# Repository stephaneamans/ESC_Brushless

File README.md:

# ESC brushless

## General principle

The electronic speed controler (ESC) is used to control the rotation and speed of a brushless motor.

Brushless motors are widely used in lot of applications.

The system is based around a microcontroler controlling a gate driver in charge of switching on and of MOS FET to power the motors inductors (see the principle the the hardware section).
The rotor position and general other informations are sent back to the microcontroller to help it to detect the appropriate timming of commutation.
The microcontroller takes informations through a bus link from the master system, mainly to know the motor speed to apply.
It can send back some informations like, current consumption, acknowledges, diagnostics and so on.

[Hardware architecture documentation](./01-documentation/hardware_architecture.md)

[Software architecture documentation](./01-documentation/software_architecture.md)

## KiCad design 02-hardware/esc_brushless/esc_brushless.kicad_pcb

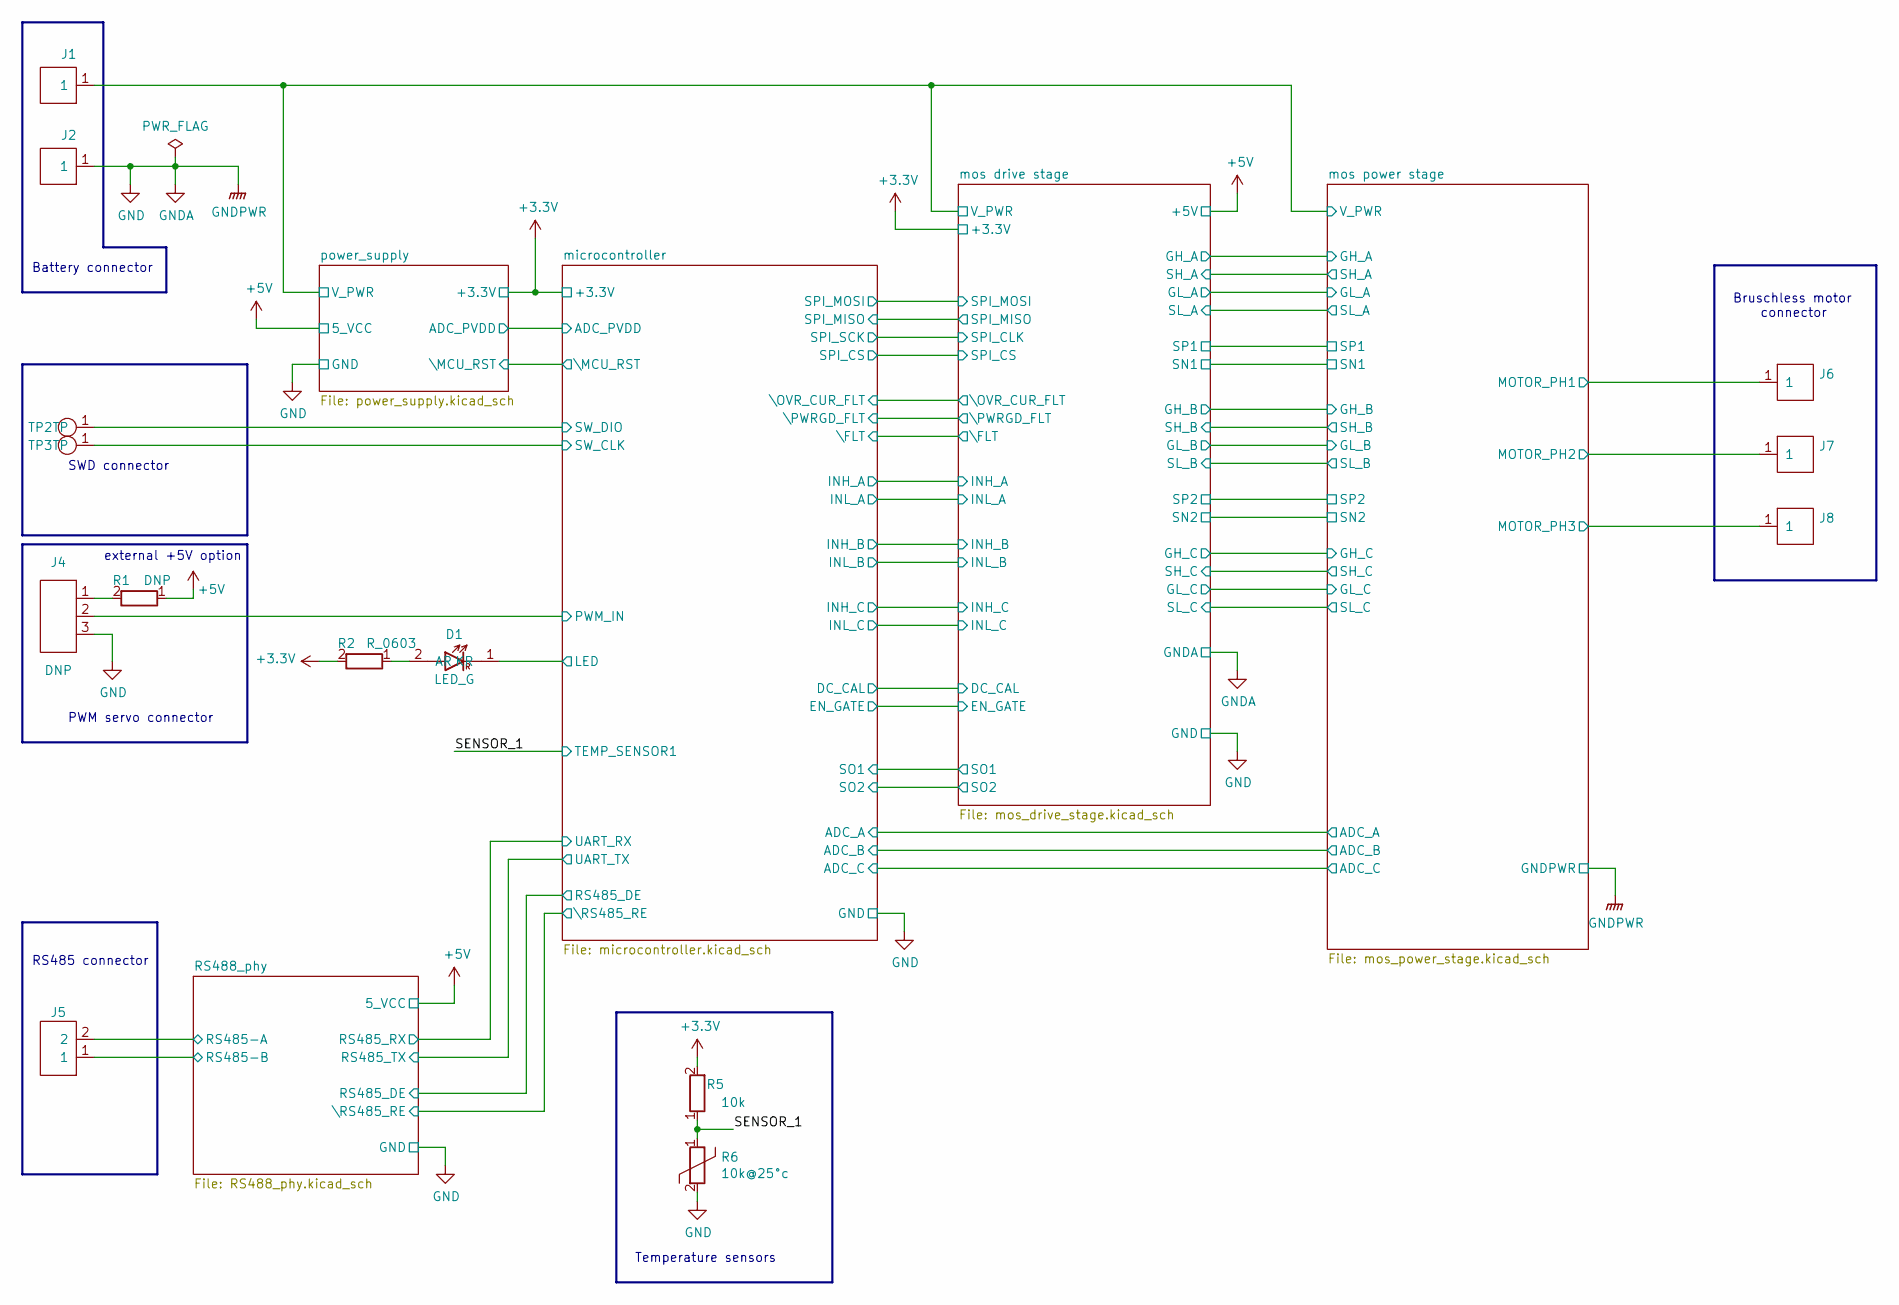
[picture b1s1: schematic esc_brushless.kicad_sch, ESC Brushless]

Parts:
D1: LED_G; LED_0603_1608Metric
J1, J2: Conn_HE13_1x1_5.08V; PinHeader_1x01_P5.08mm_Vertical
J4: DNP; PinHeader_1x03_P2.54mm_Vertical
J5: Conn_HE13_1x2_2.54V; PinHeader_1x02_P2.54mm_Vertical
J6, J7, J8: DNP; PinHeader_1x01_P5.08mm_Vertical
R1: DNP; R_0603_1608Metric_Pad0.98x0.95mm_HandSolder
R2: R_0603; R_0603_1608Metric_Pad0.98x0.95mm_HandSolder
R5: 10k; R_0603_1608Metric_Pad0.98x0.95mm_HandSolder
R6: 10k@25°c; R_0603_1608Metric_Pad0.98x0.95mm_HandSolder
TP2, TP3: test_point_smd; TP_SMD_1.25mm

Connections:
+3.3V: R2.2, R5.2; also elsewhere on the board
+5V: R1.1; also elsewhere on the board
/RS488_phy/RS485-A: J5.2; also elsewhere on the board
/RS488_phy/RS485-B: J5.1; also elsewhere on the board
/SENSOR_1: R5.1, R6.1; also elsewhere on the board
/microcontroller/LED: D1.1 (KR); also elsewhere on the board
/microcontroller/PWM_IN: J4.2; also elsewhere on the board
/microcontroller/SW_CLK: TP3.1 (TP); also elsewhere on the board
/microcontroller/SW_DIO: TP2.1 (TP); also elsewhere on the board
/mos drive stage/SH_A: J6.1; also elsewhere on the board
/mos drive stage/SH_B: J7.1; also elsewhere on the board
/mos drive stage/SH_C: J8.1; also elsewhere on the board
/mos drive stage/V_PWR: J1.1; also elsewhere on the board
GND: J2.1, J4.3, R6.2; also elsewhere on the board
unnamed: D1.2 (AR), R2.1
unnamed: J4.1, R1.2

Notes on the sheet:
Bruschless motor connector
SWD connector
PWM servo connector
RS485 connector
Temperature sensors
external +5V option
Battery connector

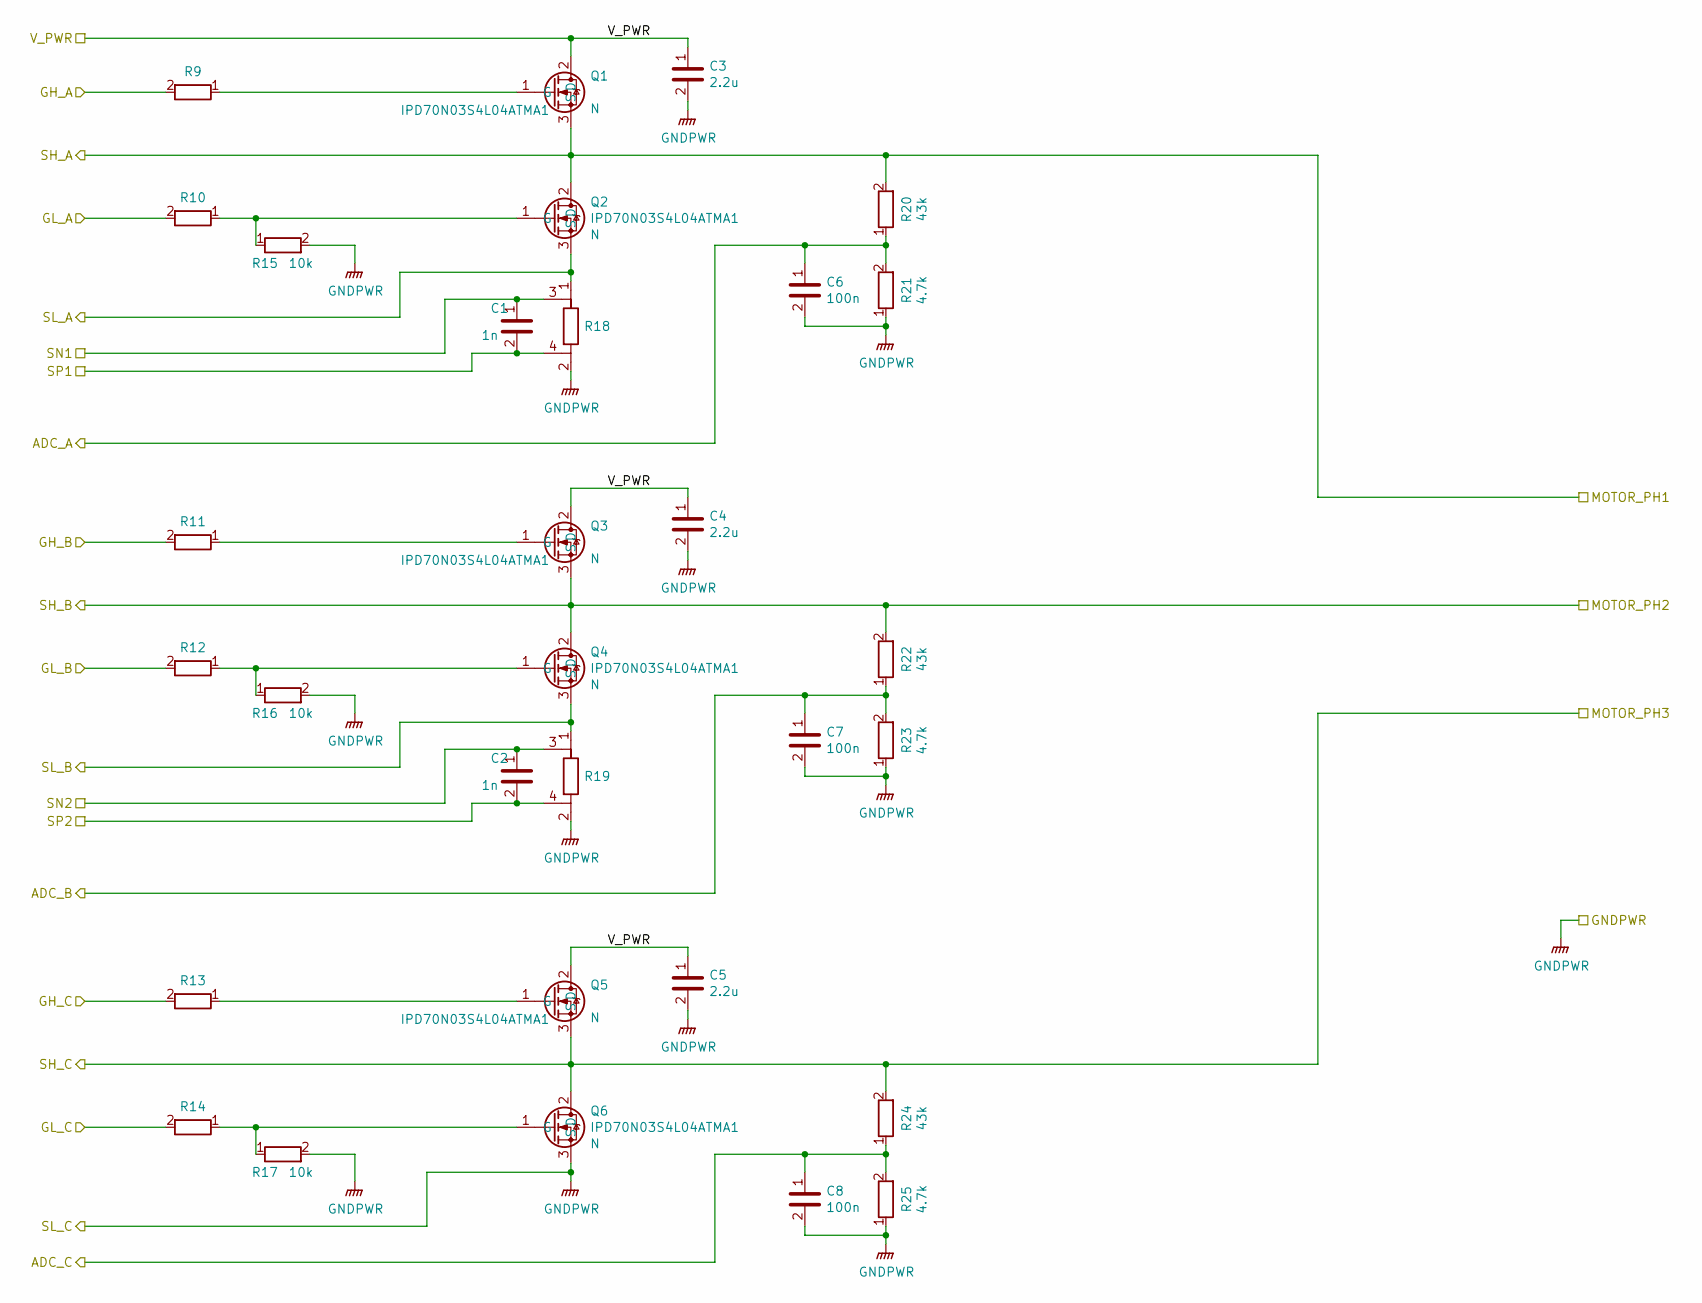
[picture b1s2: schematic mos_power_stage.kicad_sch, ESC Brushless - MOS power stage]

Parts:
C1, C2: 1n; C_0603_1608Metric_Pad1.08x0.95mm_HandSolder
C3, C4, C5: 2.2u; C_1210_3225Metric_Pad1.33x2.70mm_HandSolder
C6, C7, C8: 100n; C_0805_2012Metric_Pad1.18x1.45mm_HandSolder
Q1, Q2, Q3, Q4, Q5, Q6: IPD70N03S4L04ATMA1; TO-252-pin_1_3_TabPin2
R9, R10, R11, R12, R13, R14: R_0603; R_0603_1608Metric_Pad0.98x0.95mm_HandSolder
R15, R16, R17: 10k; R_0603_1608Metric_Pad0.98x0.95mm_HandSolder
R18, R19: R_shunt_2512; R_2512_6332Metric_shunt
R20, R22, R24: 43k; R_0603_1608Metric_Pad0.98x0.95mm_HandSolder
R21, R23, R25: 4.7k; R_0603_1608Metric_Pad0.98x0.95mm_HandSolder

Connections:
/microcontroller/ADC_A: C6.1, R20.1, R21.2; also elsewhere on the board
/microcontroller/ADC_B: C7.1, R22.1, R23.2; also elsewhere on the board
/microcontroller/ADC_C: C8.1, R24.1, R25.2; also elsewhere on the board
/mos drive stage/GH_A: R9.2; also elsewhere on the board
/mos drive stage/GH_B: R11.2; also elsewhere on the board
/mos drive stage/GH_C: R13.2; also elsewhere on the board
/mos drive stage/GL_A: R10.2; also elsewhere on the board
/mos drive stage/GL_B: R12.2; also elsewhere on the board
/mos drive stage/GL_C: R14.2; also elsewhere on the board
/mos drive stage/SH_A: Q1.3 (S), Q2.2 (D), R20.2; also elsewhere on the board
/mos drive stage/SH_B: Q3.3 (S), Q4.2 (D), R22.2; also elsewhere on the board
/mos drive stage/SH_C: Q5.3 (S), Q6.2 (D), R24.2; also elsewhere on the board
/mos drive stage/SL_A: Q2.3 (S), R18.1; also elsewhere on the board
/mos drive stage/SL_B: Q4.3 (S), R19.1; also elsewhere on the board
/mos drive stage/SN1: C1.1, R18.3; also elsewhere on the board
/mos drive stage/SN2: C2.1, R19.3; also elsewhere on the board
/mos drive stage/SP1: C1.2, R18.4; also elsewhere on the board
/mos drive stage/SP2: C2.2, R19.4; also elsewhere on the board
/mos drive stage/V_PWR: C3.1, C4.1, C5.1, Q1.2 (D), Q3.2 (D), Q5.2 (D); also elsewhere on the board
GND: C3.2, C4.2, C5.2, C6.2, C7.2, C8.2, Q6.3 (S), R15.2, R16.2, R17.2, R18.2, R19.2, R21.1, R23.1, R25.1; also elsewhere on the board
unnamed: Q1.1 (G), R9.1
unnamed: Q2.1 (G), R10.1, R15.1
unnamed: Q3.1 (G), R11.1
unnamed: Q4.1 (G), R12.1, R16.1
unnamed: Q5.1 (G), R13.1
unnamed: Q6.1 (G), R14.1, R17.1

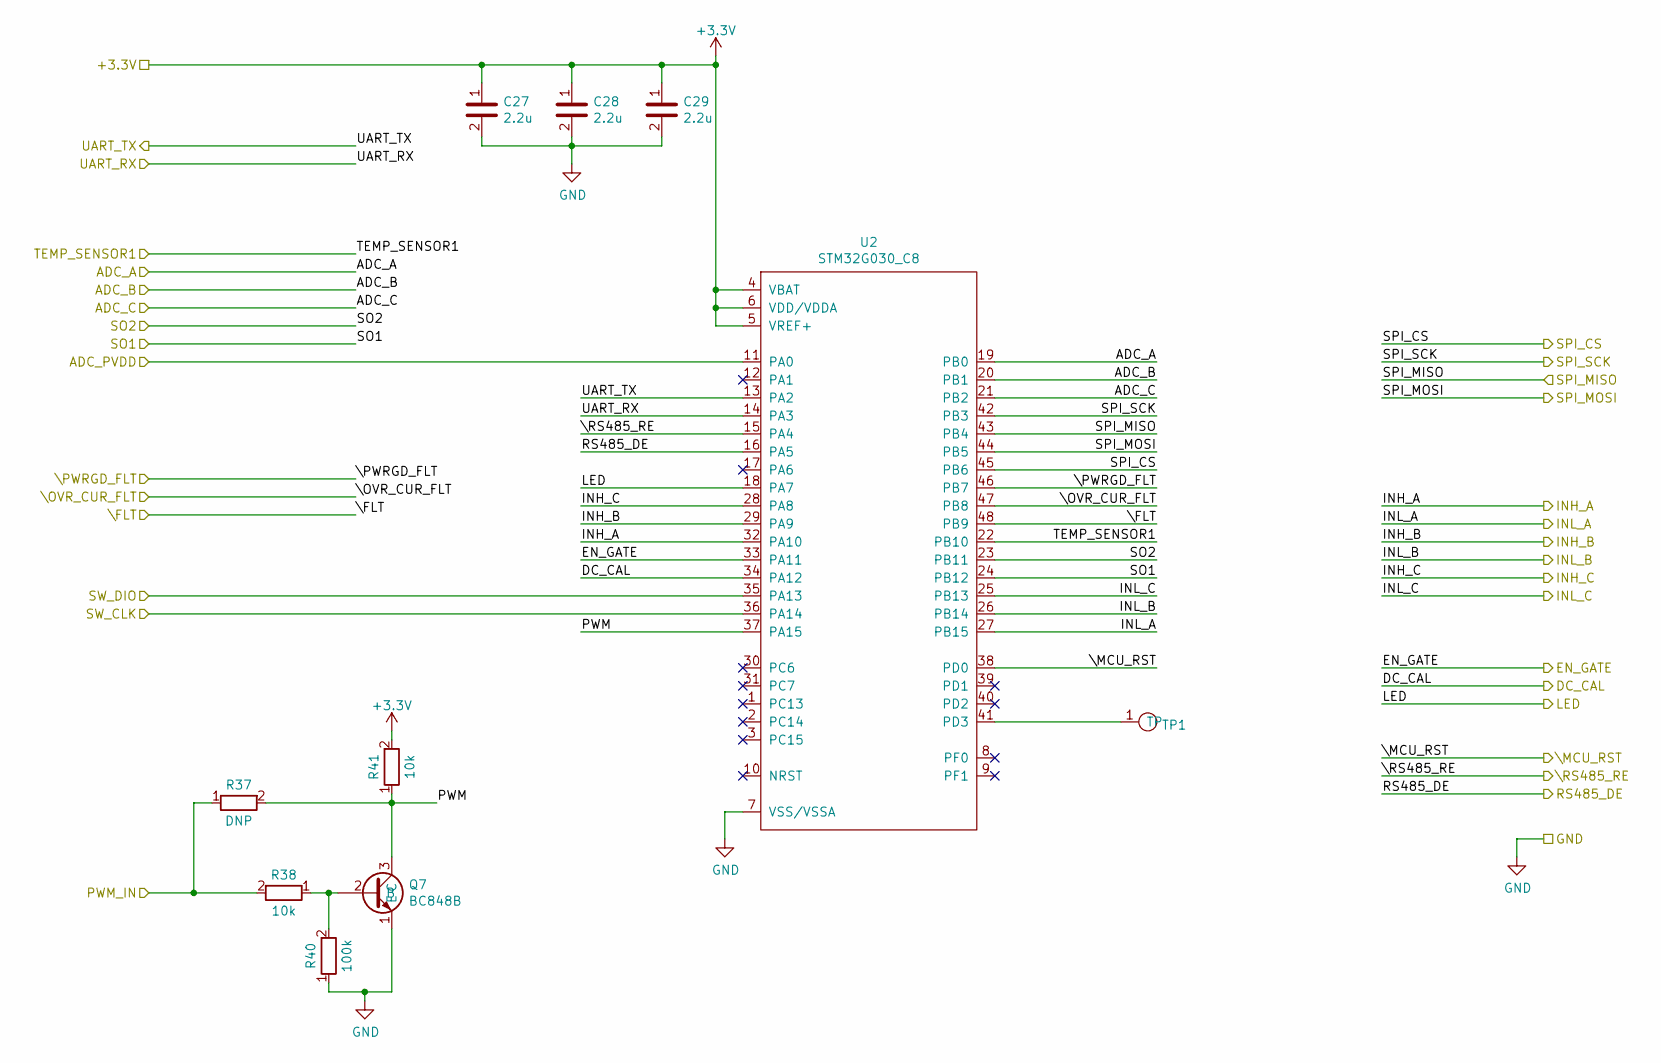
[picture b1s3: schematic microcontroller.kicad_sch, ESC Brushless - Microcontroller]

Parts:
C27, C28, C29: 2.2u; C_0603_1608Metric_Pad1.08x0.95mm_HandSolder
Q7: BC848B; SOT-23
R37: DNP; R_0603_1608Metric_Pad0.98x0.95mm_HandSolder
R38, R41: 10k; R_0603_1608Metric_Pad0.98x0.95mm_HandSolder
R40: 100k; R_0603_1608Metric_Pad0.98x0.95mm_HandSolder
TP1: test_point_smd; TP_SMD_1.25mm
U2: STM32G030_C8; LQFP-48_7x7mm_P0.5mm

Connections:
+3.3V: C27.1, C28.1, C29.1, R41.2, U2.4 (VBAT), U2.5 (VREF+), U2.6 (VDD/VDDA); also elsewhere on the board
/SENSOR_1: U2.22 (PB10); also elsewhere on the board
/microcontroller/ADC_A: U2.19 (PB0); also elsewhere on the board
/microcontroller/ADC_B: U2.20 (PB1); also elsewhere on the board
/microcontroller/ADC_C: U2.21 (PB2); also elsewhere on the board
/microcontroller/ADC_PVDD: U2.11 (PA0); also elsewhere on the board
/microcontroller/DC_CAL: U2.34 (PA12); also elsewhere on the board
/microcontroller/EN_GATE: U2.33 (PA11); also elsewhere on the board
/microcontroller/INH_A: U2.32 (PA10); also elsewhere on the board
/microcontroller/INH_B: U2.29 (PA9); also elsewhere on the board
/microcontroller/INH_C: U2.28 (PA8); also elsewhere on the board
/microcontroller/INL_A: U2.27 (PB15); also elsewhere on the board
/microcontroller/INL_B: U2.26 (PB14); also elsewhere on the board
/microcontroller/INL_C: U2.25 (PB13); also elsewhere on the board
/microcontroller/LED: U2.18 (PA7); also elsewhere on the board
/microcontroller/PWM: Q7.3 (C), R37.2, R41.1, U2.37 (PA15)
/microcontroller/PWM_IN: R37.1, R38.2; also elsewhere on the board
/microcontroller/RS485_DE: U2.16 (PA5); also elsewhere on the board
/microcontroller/SO1: U2.24 (PB12); also elsewhere on the board
/microcontroller/SO2: U2.23 (PB11); also elsewhere on the board
/microcontroller/SPI_CS: U2.45 (PB6); also elsewhere on the board
/microcontroller/SPI_MISO: U2.43 (PB4); also elsewhere on the board
/microcontroller/SPI_MOSI: U2.44 (PB5); also elsewhere on the board
/microcontroller/SPI_SCK: U2.42 (PB3); also elsewhere on the board
/microcontroller/SW_CLK: U2.36 (PA14); also elsewhere on the board
/microcontroller/SW_DIO: U2.35 (PA13); also elsewhere on the board
/microcontroller/UART_RX: U2.14 (PA3); also elsewhere on the board
/microcontroller/UART_TX: U2.13 (PA2); also elsewhere on the board
/microcontroller/\FLT: U2.48 (PB9); also elsewhere on the board
/microcontroller/\MCU_RST: U2.38 (PD0); also elsewhere on the board
/microcontroller/\OVR_CUR_FLT: U2.47 (PB8); also elsewhere on the board
/microcontroller/\PWRGD_FLT: U2.46 (PB7); also elsewhere on the board
/microcontroller/\RS485_RE: U2.15 (PA4); also elsewhere on the board
GND: C27.2, C28.2, C29.2, Q7.1 (E), R40.1, U2.7 (VSS/VSSA); also elsewhere on the board
unnamed: Q7.2 (B), R38.1, R40.2
unnamed: TP1.1 (TP), U2.41 (PD3)

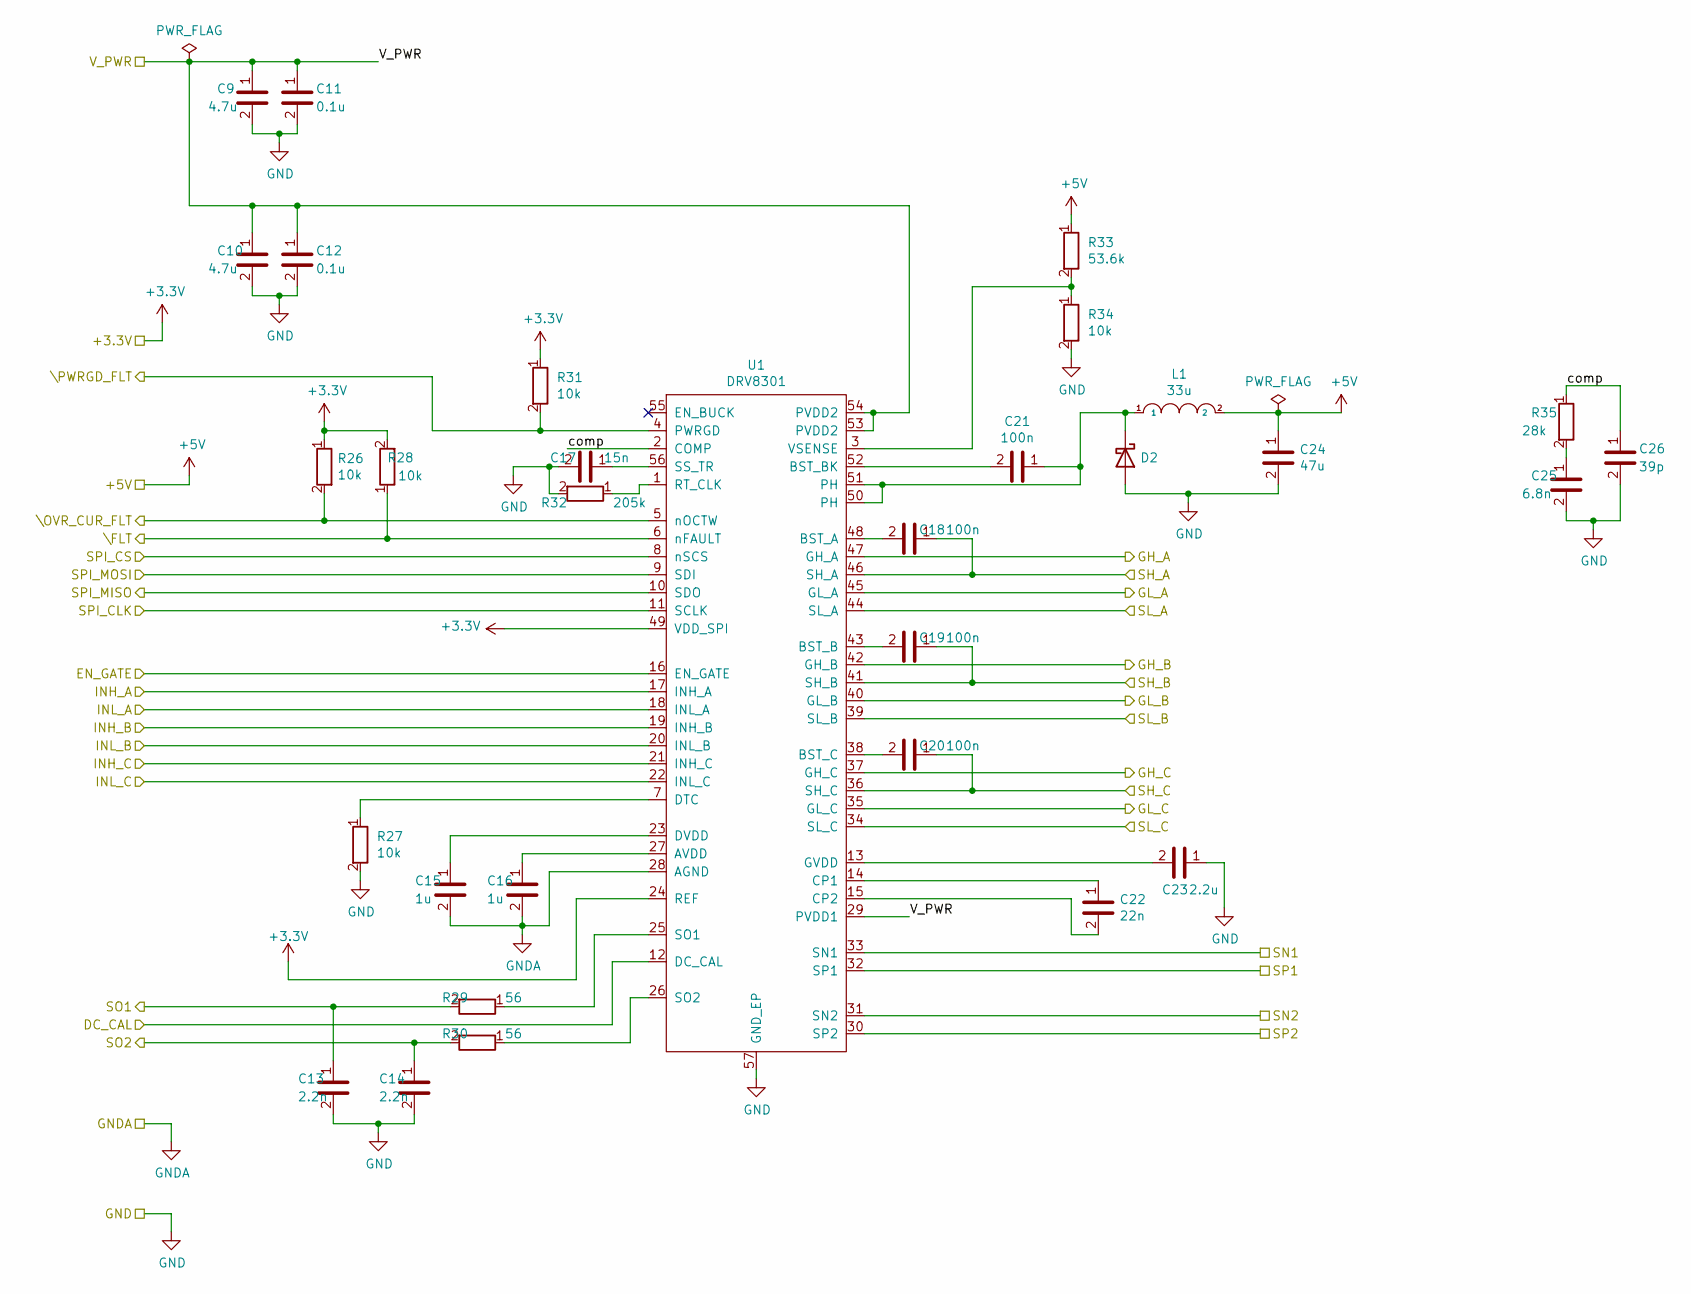
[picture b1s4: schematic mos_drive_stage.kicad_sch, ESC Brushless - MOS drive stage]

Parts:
C9, C10: 4.7u; C_1210_3225Metric_Pad1.33x2.70mm_HandSolder; Voltage 16V
C11, C12: 0.1u; C_0603_1608Metric_Pad1.08x0.95mm_HandSolder; Voltage 16V
C13, C14: 2.2n; C_0603_1608Metric_Pad1.08x0.95mm_HandSolder; Voltage 10V
C15, C16: 1u; C_0603_1608Metric_Pad1.08x0.95mm_HandSolder; Voltage 10V
C17: 15n; C_0603_1608Metric_Pad1.08x0.95mm_HandSolder; Voltage 16V
C18, C19, C20: 100n; C_0603_1608Metric_Pad1.08x0.95mm_HandSolder; Voltage 16V
C21: 100n; C_0603_1608Metric_Pad1.08x0.95mm_HandSolder
C22: 22n; C_0603_1608Metric_Pad1.08x0.95mm_HandSolder; Voltage 16V
C23: 2.2u; C_0603_1608Metric_Pad1.08x0.95mm_HandSolder; Voltage 16V
C24: 47u; C_1206_3216Metric_Pad1.33x1.80mm_HandSolder
C25: 6.8n; C_0603_1608Metric_Pad1.08x0.95mm_HandSolder; Voltage 16V
C26: 39p; C_0603_1608Metric_Pad1.08x0.95mm_HandSolder; Voltage 16V
D2: MBRS260T3G; D_SMB_Handsoldering
L1: 33u; SDR0805
R26, R27, R28, R31, R34: 10k; R_0603_1608Metric_Pad0.98x0.95mm_HandSolder
R29, R30: 56; R_0603_1608Metric_Pad0.98x0.95mm_HandSolder
R32: 205k; R_0603_1608Metric_Pad0.98x0.95mm_HandSolder
R33: 53.6k; R_0603_1608Metric_Pad0.98x0.95mm_HandSolder
R35: 28k; R_0603_1608Metric_Pad0.98x0.95mm_HandSolder
U1: DRV8301; HTSSOP-56-1EP_6.1x14mm_P0.5mm_EP3.61x6.35mm.kicad_mod

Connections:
+3.3V: R26.1, R28.2, R31.1, U1.24 (REF), U1.49 (VDD_SPI); also elsewhere on the board
+5V: C24.1, L1.2, R33.1; also elsewhere on the board
/microcontroller/DC_CAL: U1.12 (DC_CAL); also elsewhere on the board
/microcontroller/EN_GATE: U1.16 (EN_GATE); also elsewhere on the board
/microcontroller/INH_A: U1.17 (INH_A); also elsewhere on the board
/microcontroller/INH_B: U1.19 (INH_B); also elsewhere on the board
/microcontroller/INH_C: U1.21 (INH_C); also elsewhere on the board
/microcontroller/INL_A: U1.18 (INL_A); also elsewhere on the board
/microcontroller/INL_B: U1.20 (INL_B); also elsewhere on the board
/microcontroller/INL_C: U1.22 (INL_C); also elsewhere on the board
/microcontroller/SO1: C13.1, R29.2; also elsewhere on the board
/microcontroller/SO2: C14.1, R30.2; also elsewhere on the board
/microcontroller/SPI_CS: U1.8 (nSCS); also elsewhere on the board
/microcontroller/SPI_MISO: U1.10 (SDO); also elsewhere on the board
/microcontroller/SPI_MOSI: U1.9 (SDI); also elsewhere on the board
/microcontroller/SPI_SCK: U1.11 (SCLK); also elsewhere on the board
/microcontroller/\FLT: R28.1, U1.6 (nFAULT); also elsewhere on the board
/microcontroller/\OVR_CUR_FLT: R26.2, U1.5 (nOCTW); also elsewhere on the board
/microcontroller/\PWRGD_FLT: R31.2, U1.4 (PWRGD); also elsewhere on the board
/mos drive stage/GH_A: U1.47 (GH_A); also elsewhere on the board
/mos drive stage/GH_B: U1.42 (GH_B); also elsewhere on the board
/mos drive stage/GH_C: U1.37 (GH_C); also elsewhere on the board
/mos drive stage/GL_A: U1.45 (GL_A); also elsewhere on the board
/mos drive stage/GL_B: U1.40 (GL_B); also elsewhere on the board
/mos drive stage/GL_C: U1.35 (GL_C); also elsewhere on the board
/mos drive stage/SH_A: C18.1, U1.46 (SH_A); also elsewhere on the board
/mos drive stage/SH_B: C19.1, U1.41 (SH_B); also elsewhere on the board
/mos drive stage/SH_C: C20.1, U1.36 (SH_C); also elsewhere on the board
/mos drive stage/SL_A: U1.44 (SL_A); also elsewhere on the board
/mos drive stage/SL_B: U1.39 (SL_B); also elsewhere on the board
/mos drive stage/SN1: U1.33 (SN1); also elsewhere on the board
/mos drive stage/SN2: U1.31 (SN2); also elsewhere on the board
/mos drive stage/SP1: U1.32 (SP1); also elsewhere on the board
/mos drive stage/SP2: U1.30 (SP2); also elsewhere on the board
/mos drive stage/V_PWR: C9.1, C10.1, C11.1, C12.1, U1.29 (PVDD1), U1.53 (PVDD2), U1.54 (PVDD2); also elsewhere on the board
/mos drive stage/comp: C26.1, R35.1, U1.2 (COMP)
GND: C9.2, C10.2, C11.2, C12.2, C13.2, C14.2, C15.2, C16.2, C17.2, C23.1, C24.2, C25.2, C26.2, D2.2 (A), R27.2, R32.2, R34.2, U1.28 (AGND), U1.34 (SL_C), U1.57 (GND_EP); also elsewhere on the board
unnamed: C15.1, U1.23 (DVDD)
unnamed: C16.1, U1.27 (AVDD)
unnamed: C17.1, U1.56 (SS_TR)
unnamed: C18.2, U1.48 (BST_A)
unnamed: C19.2, U1.43 (BST_B)
unnamed: C20.2, U1.38 (BST_C)
unnamed: C21.1, D2.1 (K), L1.1, U1.50 (PH), U1.51 (PH)
unnamed: C21.2, U1.52 (BST_BK)
unnamed: C22.1, U1.14 (CP1)
unnamed: C22.2, U1.15 (CP2)
unnamed: C23.2, U1.13 (GVDD)
unnamed: C25.1, R35.2
unnamed: R27.1, U1.7 (DTC)
unnamed: R29.1, U1.25 (SO1)
unnamed: R30.1, U1.26 (SO2)
unnamed: R32.1, U1.1 (RT_CLK)
unnamed: R33.2, R34.1, U1.3 (VSENSE)

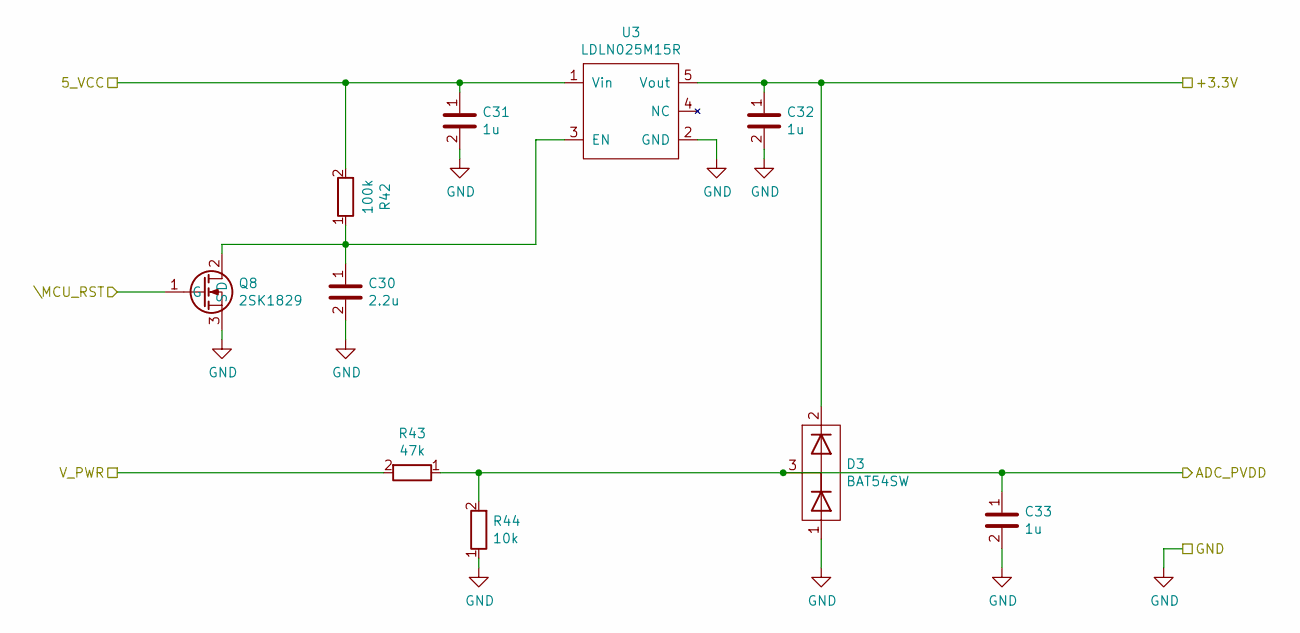
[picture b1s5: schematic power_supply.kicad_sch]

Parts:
C30: 2.2u; C_0603_1608Metric_Pad1.08x0.95mm_HandSolder
C31, C32, C33: 1u; C_0603_1608Metric_Pad1.08x0.95mm_HandSolder
D3: BAT54SW; SOT-323
Q8: 2SK1829; SOT-23
R42: 100k; R_0603_1608Metric_Pad0.98x0.95mm_HandSolder
R43: 47k; R_0603_1608Metric_Pad0.98x0.95mm_HandSolder
R44: 10k; R_0603_1608Metric_Pad0.98x0.95mm_HandSolder
U3: LDLN025M15R; SOT-23-5

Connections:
+3.3V: C32.1, D3.2 (K), U3.5 (Vout); also elsewhere on the board
+5V: C31.1, R42.2, U3.1 (Vin); also elsewhere on the board
/microcontroller/ADC_PVDD: C33.1, D3.3 (A/K), R43.1, R44.2; also elsewhere on the board
/microcontroller/\MCU_RST: Q8.1 (G); also elsewhere on the board
/mos drive stage/V_PWR: R43.2; also elsewhere on the board
GND: C30.2, C31.2, C32.2, C33.2, D3.1 (A), Q8.3 (S), R44.1, U3.2 (GND); also elsewhere on the board
unnamed: C30.1, Q8.2 (D), R42.1, U3.3 (EN)

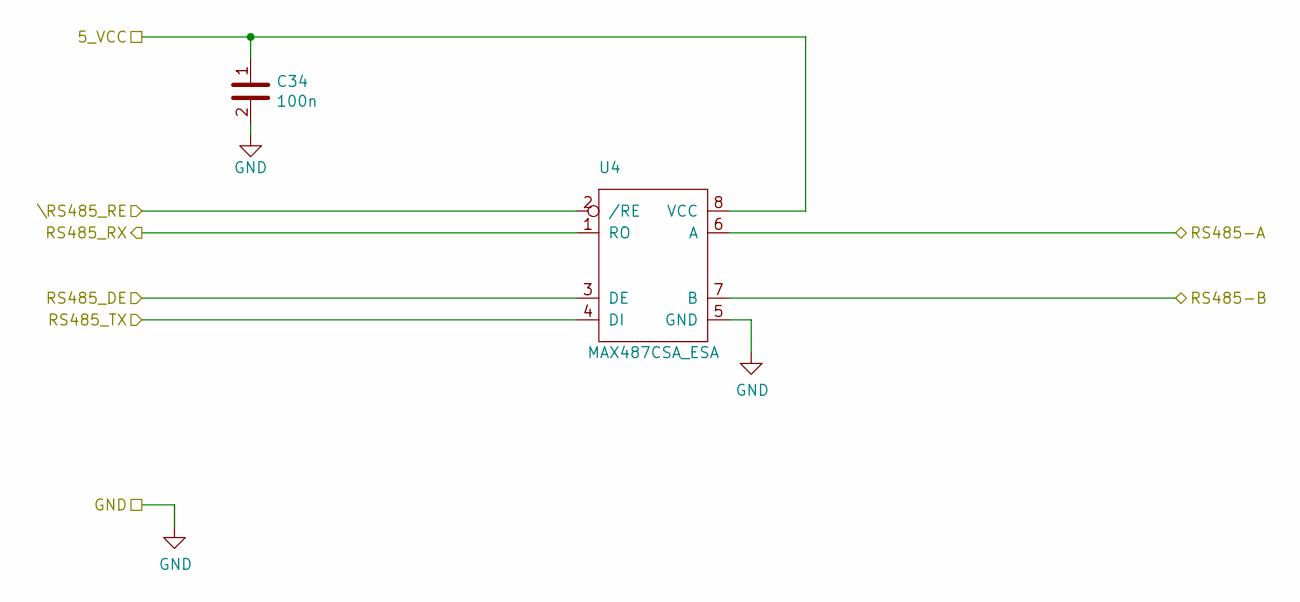
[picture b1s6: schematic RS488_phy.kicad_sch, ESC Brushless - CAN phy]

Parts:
C34: 100n; C_0603_1608Metric_Pad1.08x0.95mm_HandSolder
U4: MAX487CSA_ESA; SOIC-8_3.9x4.9mm_P1.27mm

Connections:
+5V: C34.1, U4.8 (VCC); also elsewhere on the board
/RS488_phy/RS485-A: U4.6 (A); also elsewhere on the board
/RS488_phy/RS485-B: U4.7 (B); also elsewhere on the board
/microcontroller/RS485_DE: U4.3 (DE); also elsewhere on the board
/microcontroller/UART_RX: U4.1 (RO); also elsewhere on the board
/microcontroller/UART_TX: U4.4 (DI); also elsewhere on the board
/microcontroller/\RS485_RE: U4.2 (/RE); also elsewhere on the board
GND: C34.2, U4.5 (GND); also elsewhere on the board

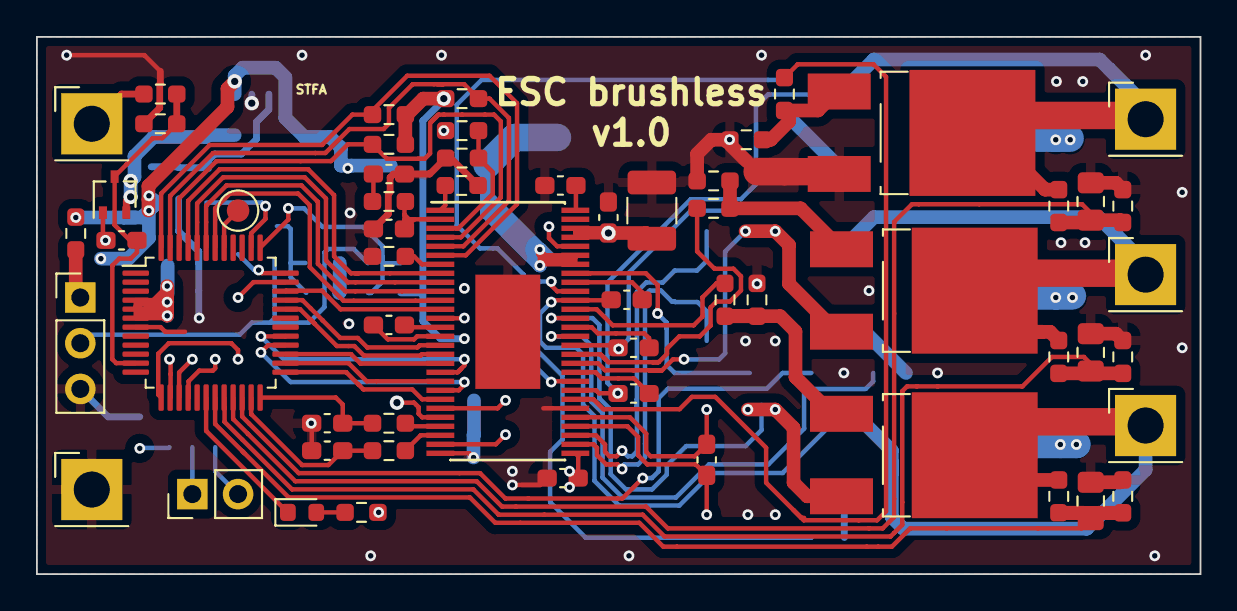
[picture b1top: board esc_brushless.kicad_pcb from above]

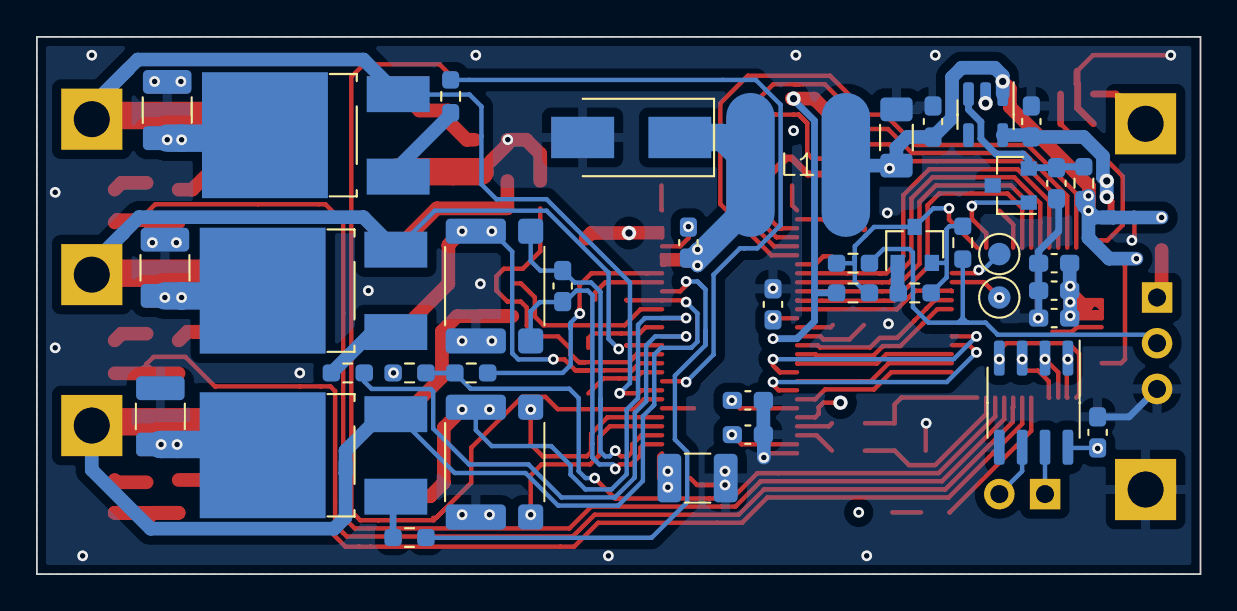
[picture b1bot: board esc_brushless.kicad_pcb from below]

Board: 4 copper layers, 64.6 x 29.8 mm, 98 parts (40 on the bottom side), 82 nets.

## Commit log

2021-02-09 HW - Add IPD30N03S4L_09 ouptput stage simulation
2021-03-14 Schematics v1.0 - Architecture, MOS power stage, mos driver stage and RS485 interface
2021-04-25 Schematics v1.0 - Architecture, microcontroler, global interconnections and IO
2021-04-26 Schematics v1.0 - Architecture, LED, test
2021-04-29 Schematics v1.0 - Fix DRC issues
2021-05-01 Schematics v1.0 - Remove some options and test points
2021-08-09 Schematics v1.0 - PCB layout v1.0
2021-12-06 Schematics v1.0 - Architecture V1.0, fix DRC issues
2021-12-06 PCB layout v1.0 - Place and route the board layout
2021-12-06 PCB layout v1.0 - Gerber generation
2022-08-14 Schematic and PCB v1.1.0 - Converted to KiCAD6, all DRC cleared
2024-06-21 Added bldc_motor_topologies.svg
2024-06-21 Added Untitled Diagram.drawio.svg
2024-06-21 Added bldc_motor_topologies.drawio.svg
2024-06-21 Added esc_commutation_principle.drawio.svg
